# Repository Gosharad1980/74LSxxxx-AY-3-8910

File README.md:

# 74LSxxxx-AY-3-8910
Discrete 74LSxxxx study of an AY-3-8910 vintage sound chip 

Only the schematic was written
No PCB available in the KiCad project

Based on the https://github.com/mengstr/Discrete-AY-3-8910.git project

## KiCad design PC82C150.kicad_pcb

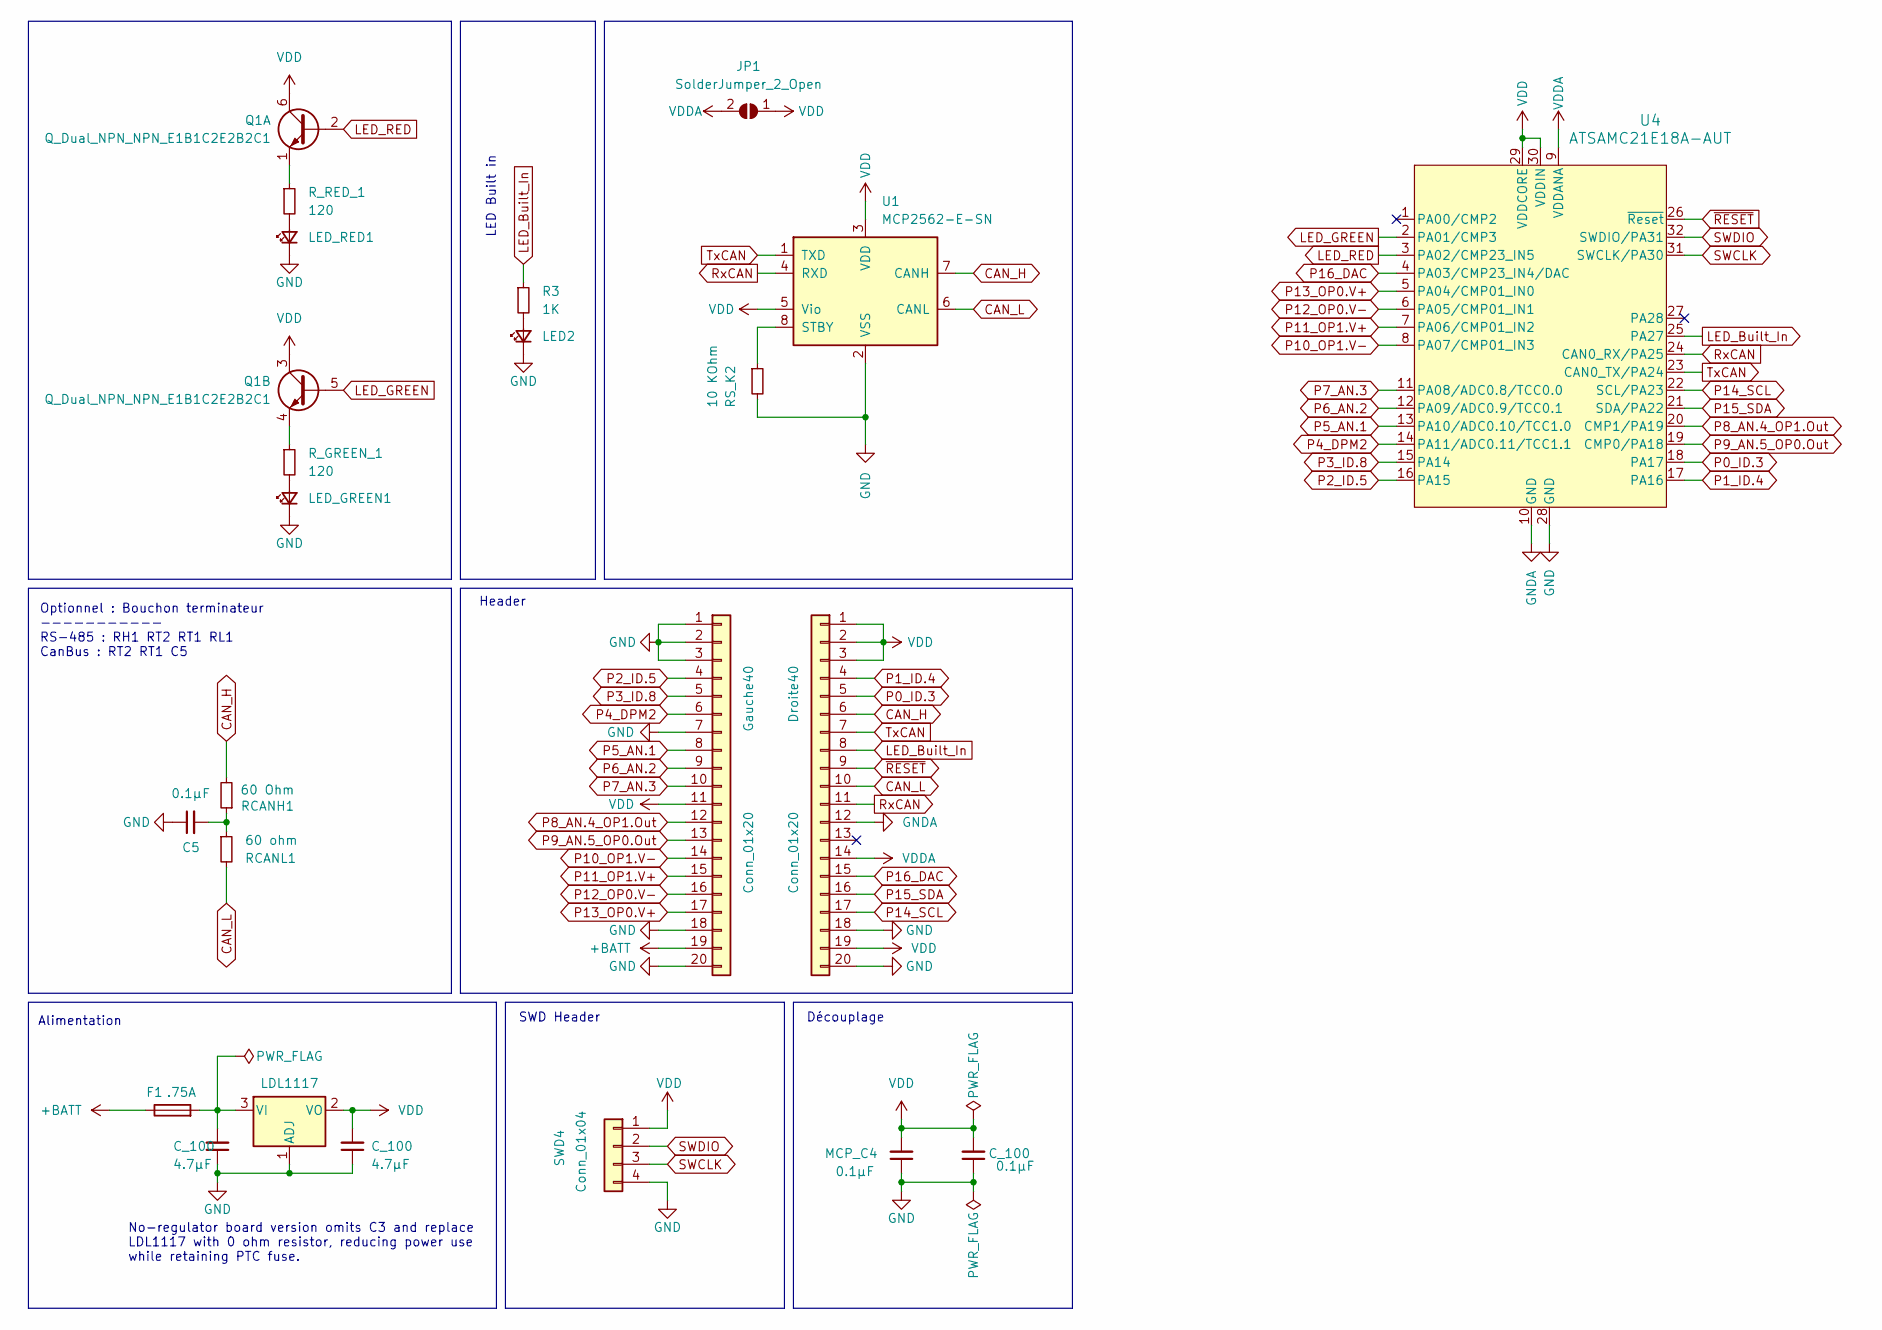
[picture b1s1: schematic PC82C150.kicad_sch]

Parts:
C5: 0.1µF; C_1206_3216Metric_Pad1.33x1.80mm_HandSolder
C_100: 4.7µF; C_1206_3216Metric_Pad1.33x1.80mm_HandSolder
Droite40: Conn_01x20; PinHeader_1x20_P2.54mm_Vertical
F1: .75A; Fuse_1206_3216Metric_Pad1.42x1.75mm_HandSolder
Gauche40: Conn_01x20; PinHeader_1x20_P2.54mm_Vertical
JP1: SolderJumper_2_Open; SolderJumper-2_P1.3mm_Open_RoundedPad1.0x1.5mm
LDL1117: LDL1117; SOT-223-3_TabPin2
LED2: LED; LED_1206_3216Metric_Pad1.42x1.75mm_HandSolder
LED_GREEN1: LED; LED_1206_3216Metric_Pad1.42x1.75mm_HandSolder
LED_RED1: LED; LED_1206_3216Metric_Pad1.42x1.75mm_HandSolder
MCP_C4: 0.1µF; C_1206_3216Metric_Pad1.33x1.80mm_HandSolder
Q1: Q_Dual_NPN_NPN_E1B1C2E2B2C1; SOT-363_SC-70-6_Handsoldering
R3: 1K; R_1206_3216Metric_Pad1.30x1.75mm_HandSolder
RCANH1: 60 Ohm; R_1206_3216Metric_Pad1.30x1.75mm_HandSolder
RCANL1: 60 ohm; R_1206_3216Metric_Pad1.30x1.75mm_HandSolder
RS_K2: 10 KOhm; R_1206_3216Metric_Pad1.30x1.75mm_HandSolder
R_GREEN_1: 120; R_1206_3216Metric_Pad1.30x1.75mm_HandSolder
R_RED_1: 120; R_1206_3216Metric_Pad1.30x1.75mm_HandSolder
SWD4: Conn_01x04; PinHeader_1x04_P2.54mm_Vertical
U1: MCP2562-E-SN; SOIC-8_3.9x4.9mm_P1.27mm
U4: ATSAMC21E18A-AUT; TQFP32_MC_MCH

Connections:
+BATT: F1.1, Gauche40.19
CAN_H: Droite40.6, RCANH1.2, U1.7 (CANH)
CAN_L: Droite40.10, RCANL1.2, U1.6 (CANL)
GND: C5.1, Droite40.18, Droite40.20, Gauche40.1, Gauche40.2, Gauche40.3, Gauche40.7, Gauche40.18, Gauche40.20, LDL1117.1 (ADJ), LED2.1 (K), LED_GREEN1.1 (K), LED_RED1.1 (K), MCP_C4.1, RS_K2.2, SWD4.4, U1.2 (VSS), U4.28 (GND); also elsewhere on the board
GNDA: Droite40.12, U4.10 (GND)
LED_Built_In: Droite40.8, R3.1, U4.25 (PA27)
LED_GREEN: Q1.5 (B2), U4.2 (PA01/CMP3)
LED_RED: Q1.2 (B1), U4.3 (PA02/CMP23_IN5)
unnamed: C5.2, RCANH1.1, RCANL1.1
unnamed 9: F1.2, LDL1117.3 (VI); also elsewhere on the board
unnamed: LED2.2 (A), R3.2
unnamed: LED_GREEN1.2 (A), R_GREEN_1.2
unnamed: LED_RED1.2 (A), R_RED_1.2
unnamed: Q1.1 (E1), R_RED_1.1
unnamed: Q1.4 (E2), R_GREEN_1.1
unnamed: RS_K2.1, U1.8 (STBY)
P0_ID.3: Droite40.5, U4.18 (PA17)
P1_ID.4: Droite40.4, U4.17 (PA16)
P2_ID.5: Gauche40.4, U4.16 (PA15)
P3_ID.8: Gauche40.5, U4.15 (PA14)
P4_DPM2: Gauche40.6, U4.14 (PA11/ADC0.11/TCC1.1)
P5_AN.1: Gauche40.8, U4.13 (PA10/ADC0.10/TCC1.0)
P6_AN.2: Gauche40.9, U4.12 (PA09/ADC0.9/TCC0.1)
P7_AN.3: Gauche40.10, U4.11 (PA08/ADC0.8/TCC0.0)
P8_AN.4_OP1.Out: Gauche40.12, U4.20 (CMP1/PA19)
P9_AN.5_OP0.Out: Gauche40.13, U4.19 (CMP0/PA18)
P10_OP1.V-: Gauche40.14, U4.8 (PA07/CMP01_IN3)
P11_OP1.V+: Gauche40.15, U4.7 (PA06/CMP01_IN2)
P12_OP0.V-: Gauche40.16, U4.6 (PA05/CMP01_IN1)
P13_OP0.V+: Gauche40.17, U4.5 (PA04/CMP01_IN0)
P14_SCL: Droite40.17, U4.22 (SCL/PA23)
P15_SDA: Droite40.16, U4.21 (SDA/PA22)
P16_DAC: Droite40.15, U4.4 (PA03/CMP23_IN4/DAC)
RxCAN: Droite40.11, U1.4 (RXD), U4.24 (CAN0_RX/PA25)
SWCLK: SWD4.3, U4.31 (SWCLK/PA30)
SWDIO: SWD4.2, U4.32 (SWDIO/PA31)
TxCAN: Droite40.7, U1.1 (TXD), U4.23 (CAN0_TX/PA24)
VDD: Droite40.1, Droite40.2, Droite40.3, Droite40.19, Gauche40.11, JP1.1 (A), LDL1117.2 (VO), MCP_C4.2, Q1.3 (C2), Q1.6 (C1), SWD4.1, U1.3 (VDD), U1.5 (Vio), U4.29 (VDDCORE), U4.30 (VDDIN); also elsewhere on the board
VDDA: Droite40.14, JP1.2 (B), U4.9 (VDDANA)
~RESET: Droite40.9, U4.26 (~Reset)

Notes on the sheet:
Alimentation
Header
LED Built in
No-regulator board version omits C3 and replace LDL1117 with 0 ohm resistor, reducing power use while retaining PTC fuse.
SWD Header
Découplage
Optionnel : Bouchon terminateur ----------- RS-485 : RH1 RT2 RT1 RL1 CanBus : RT2 RT1 C5

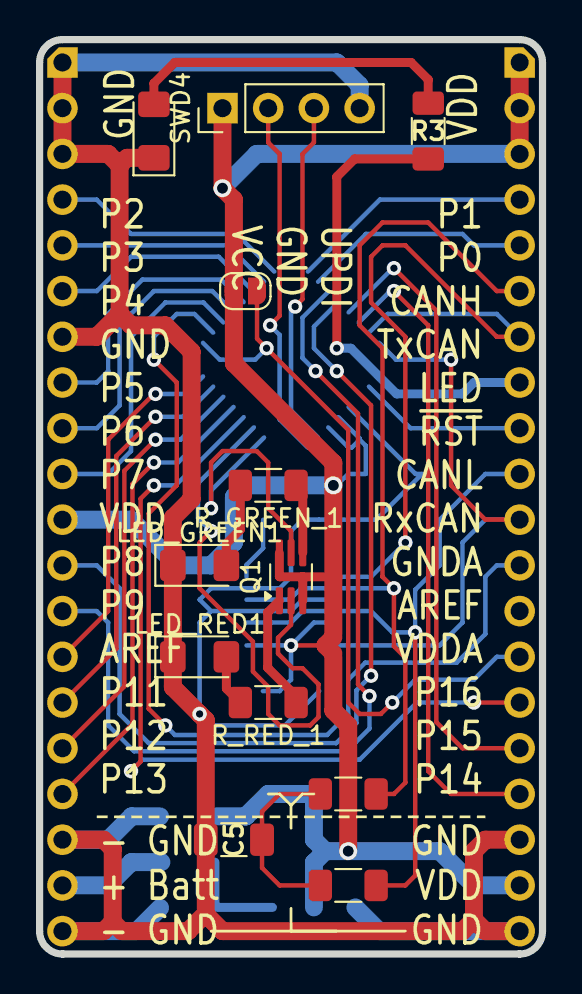
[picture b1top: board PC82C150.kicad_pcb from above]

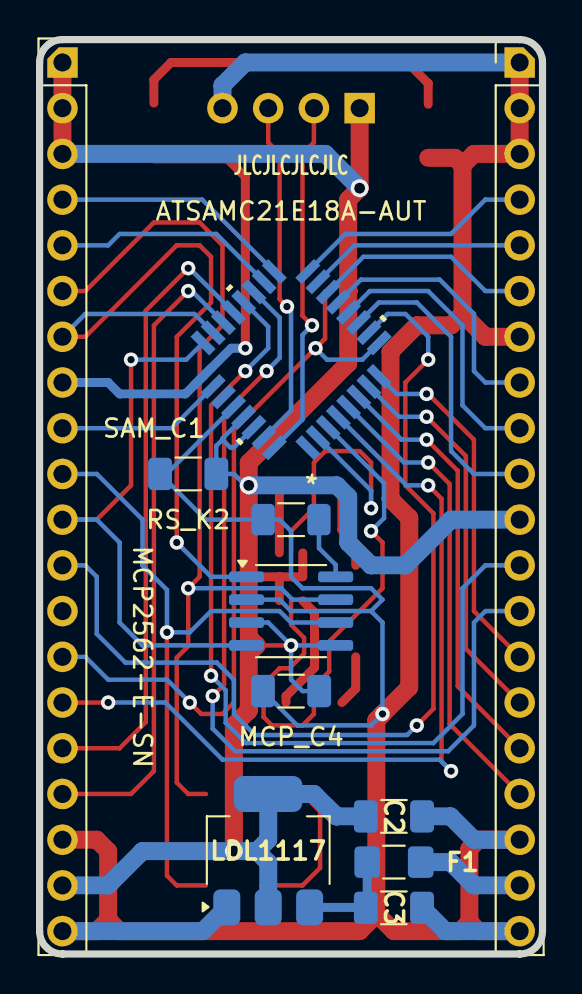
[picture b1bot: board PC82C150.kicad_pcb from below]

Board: 2 copper layers, 27.9 x 50.8 mm, 23 parts (11 on the bottom side), 40 nets.

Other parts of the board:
C2, C3: 4.7µF; C_1206_3216Metric_Pad1.33x1.80mm_HandSolder
SAM_C1: 0.1µF; C_1206_3216Metric_Pad1.33x1.80mm_HandSolder

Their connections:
GND: C2.1, C3.1, SAM_C1.1; also elsewhere on the board
unnamed 9: C3.2; also elsewhere on the board
VDD: C2.2, SAM_C1.2; also elsewhere on the board

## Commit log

2025-03-14 On init
2025-03-14 Premier commit avant branching
2025-03-14 On écrase et on remplace avec la seconde carte gérée dans ce repo
2025-03-14 Fin de création de tous les schémas - envelope.kicad_sch - EnvelopeRate.kicad_sch
2025-03-14 readme.md
2025-03-15 Correction sous-page Tone.kicad_sch
2025-04-01 CORRECTION : quelque câblages qui semblent à corriger
